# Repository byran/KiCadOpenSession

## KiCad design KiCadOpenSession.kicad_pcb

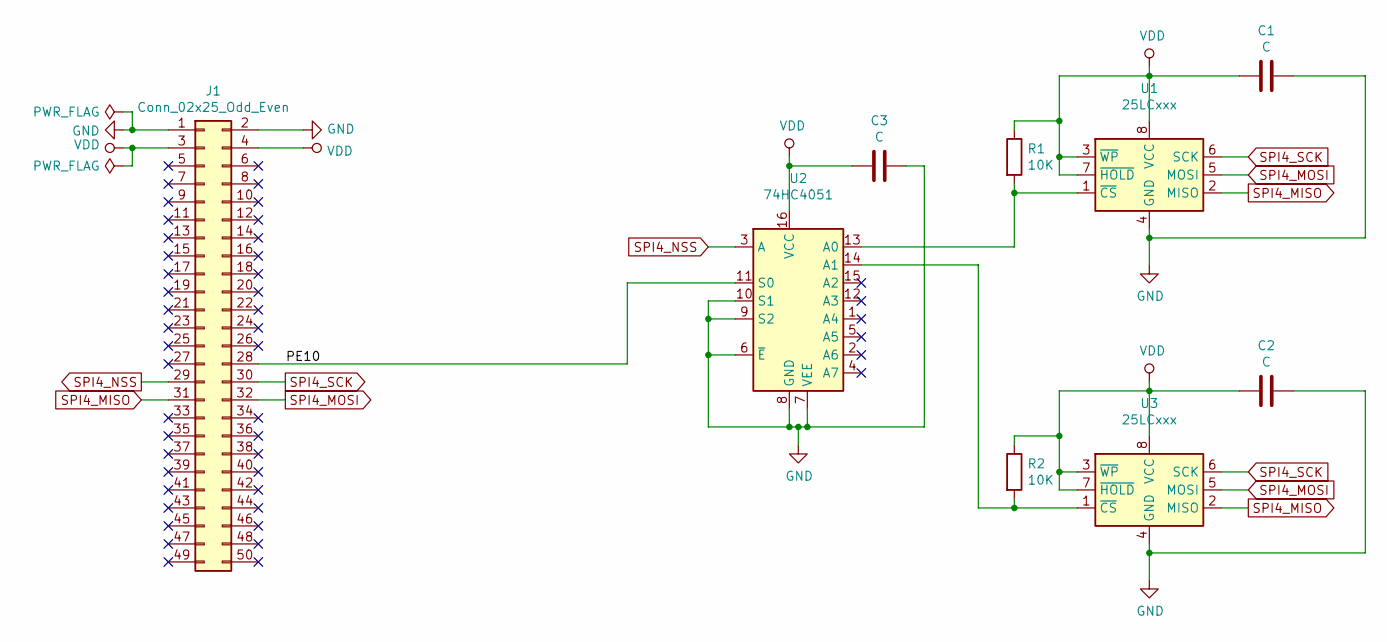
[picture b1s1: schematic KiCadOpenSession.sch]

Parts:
C1, C2, C3: C; C_0805_2012Metric_Pad1.15x1.40mm_HandSolder
J1: Conn_02x25_Odd_Even; PinSocket_2x25_P2.54mm_Vertical_Mirrored
R1, R2: 10K; R_0805_2012Metric_Pad1.15x1.40mm_HandSolder
U1, U3: 25LCxxx; SOIC-8_3.9x4.9mm_P1.27mm
U2: 74HC4051; SOIC-16_3.9x9.9mm_P1.27mm

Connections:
/PE10: J1.28, U2.11 (S0)
GND: C1.1, C2.1, C3.1, J1.1, J1.2, U1.4 (GND), U2.6 (~E), U2.7 (VEE), U2.8 (GND), U2.9 (S2), U2.10 (S1), U3.4 (GND)
unnamed: R1.2, U1.1 (~CS), U2.13 (A0)
unnamed: R2.2, U2.14 (A1), U3.1 (~CS)
SPI4_MISO: J1.31, U1.2 (MISO), U3.2 (MISO)
SPI4_MOSI: J1.32, U1.5 (MOSI), U3.5 (MOSI)
SPI4_NSS: J1.29, U2.3 (A)
SPI4_SCK: J1.30, U1.6 (SCK), U3.6 (SCK)
VDD: C1.2, C2.2, C3.2, J1.3, J1.4, R1.1, R2.1, U1.3 (~WP), U1.7 (~HOLD), U1.8 (VCC), U2.16 (VCC), U3.3 (~WP), U3.7 (~HOLD), U3.8 (VCC)

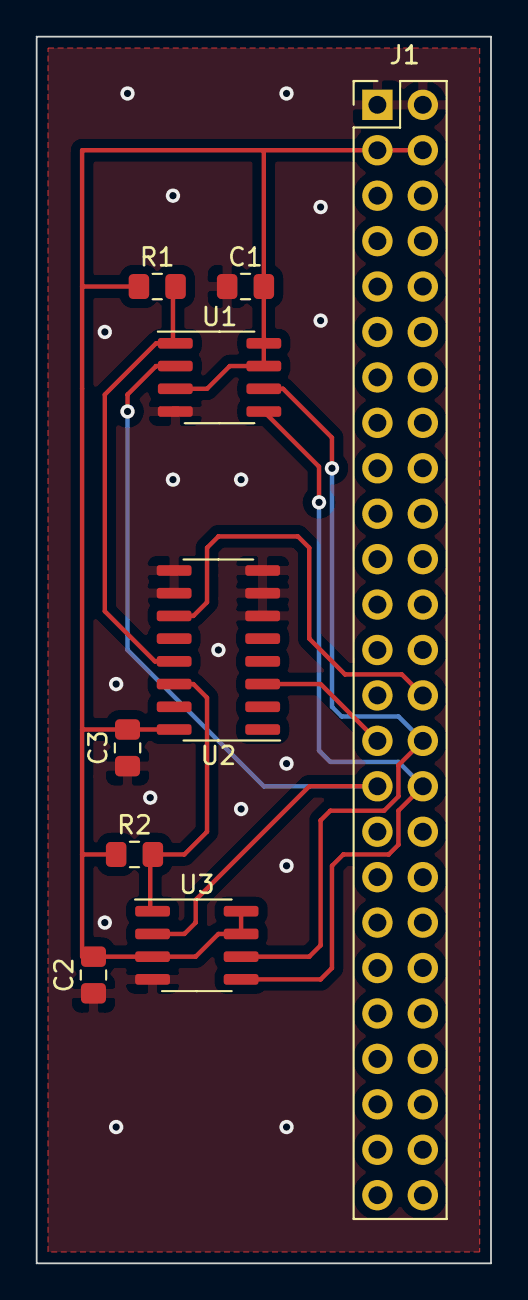
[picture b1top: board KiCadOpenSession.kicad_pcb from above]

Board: 2 copper layers, 25.4 x 68.6 mm, 9 parts (0 on the bottom side), 9 nets.

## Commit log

2020-08-30 Complete project for open session
2020-08-30 Remove DigiKey libraries that were not used in this project
2020-08-30 Add ibom
2020-08-30 Add STM32F411 Discovery board datasheets
2020-08-30 Reroute some PCB tracks and switch 5V for VDD
2020-09-06 Rename project and files to KiCadOpenSession
2020-09-26 Add smoothing capacitors
2020-09-28 Add Freeplane mind map
2020-09-28 Update mind map after run through
2020-09-28 Add PDFs of schematic and PCB
